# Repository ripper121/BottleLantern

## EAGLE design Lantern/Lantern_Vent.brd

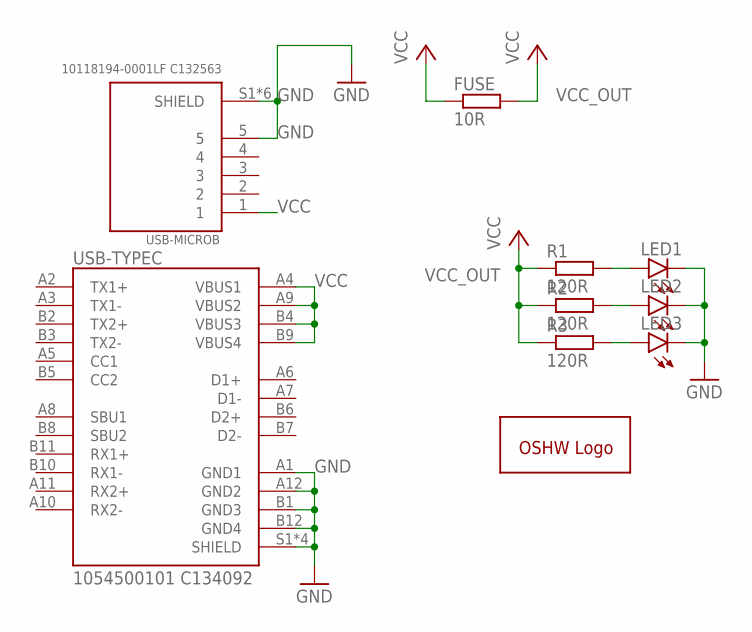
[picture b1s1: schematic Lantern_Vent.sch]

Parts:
FUSE: 10R; R0805
GOLD_ORB_SM1: OSHWLOGOLOGO5MM; OSHW_5MM
LED1, LED2, LED3: LEDCHIP-LED0805; CHIP-LED0805
R1, R2, R3: 120R; R0805
USB-MICROB: 10118194-0001LF C132563; AMPHENOL_10118194-0001LF
USB-TYPEC: 1054500101 C134092; MOLEX_105450-0101

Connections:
GND: LED1.C, LED2.C, LED3.C, USB-MICROB.5, USB-MICROB.S1 (SHIELD), USB-MICROB.S2 (SHIELD), USB-MICROB.S3 (SHIELD), USB-MICROB.S4 (SHIELD), USB-MICROB.S5 (SHIELD), USB-MICROB.S6 (SHIELD), USB-TYPEC.A1 (GND1), USB-TYPEC.A12 (GND2), USB-TYPEC.B1 (GND3), USB-TYPEC.B12 (GND4), USB-TYPEC.S1 (SHIELD), USB-TYPEC.S2 (SHIELD), USB-TYPEC.S3 (SHIELD), USB-TYPEC.S4 (SHIELD)
unnamed: LED1.A, R1.2
unnamed: LED2.A, R2.2
unnamed: LED3.A, R3.2
VCC: FUSE.1, USB-MICROB.1, USB-TYPEC.A4 (VBUS1), USB-TYPEC.A9 (VBUS2), USB-TYPEC.B4 (VBUS3), USB-TYPEC.B9 (VBUS4)
VCC_OUT: FUSE.2, R1.1, R2.1, R3.1

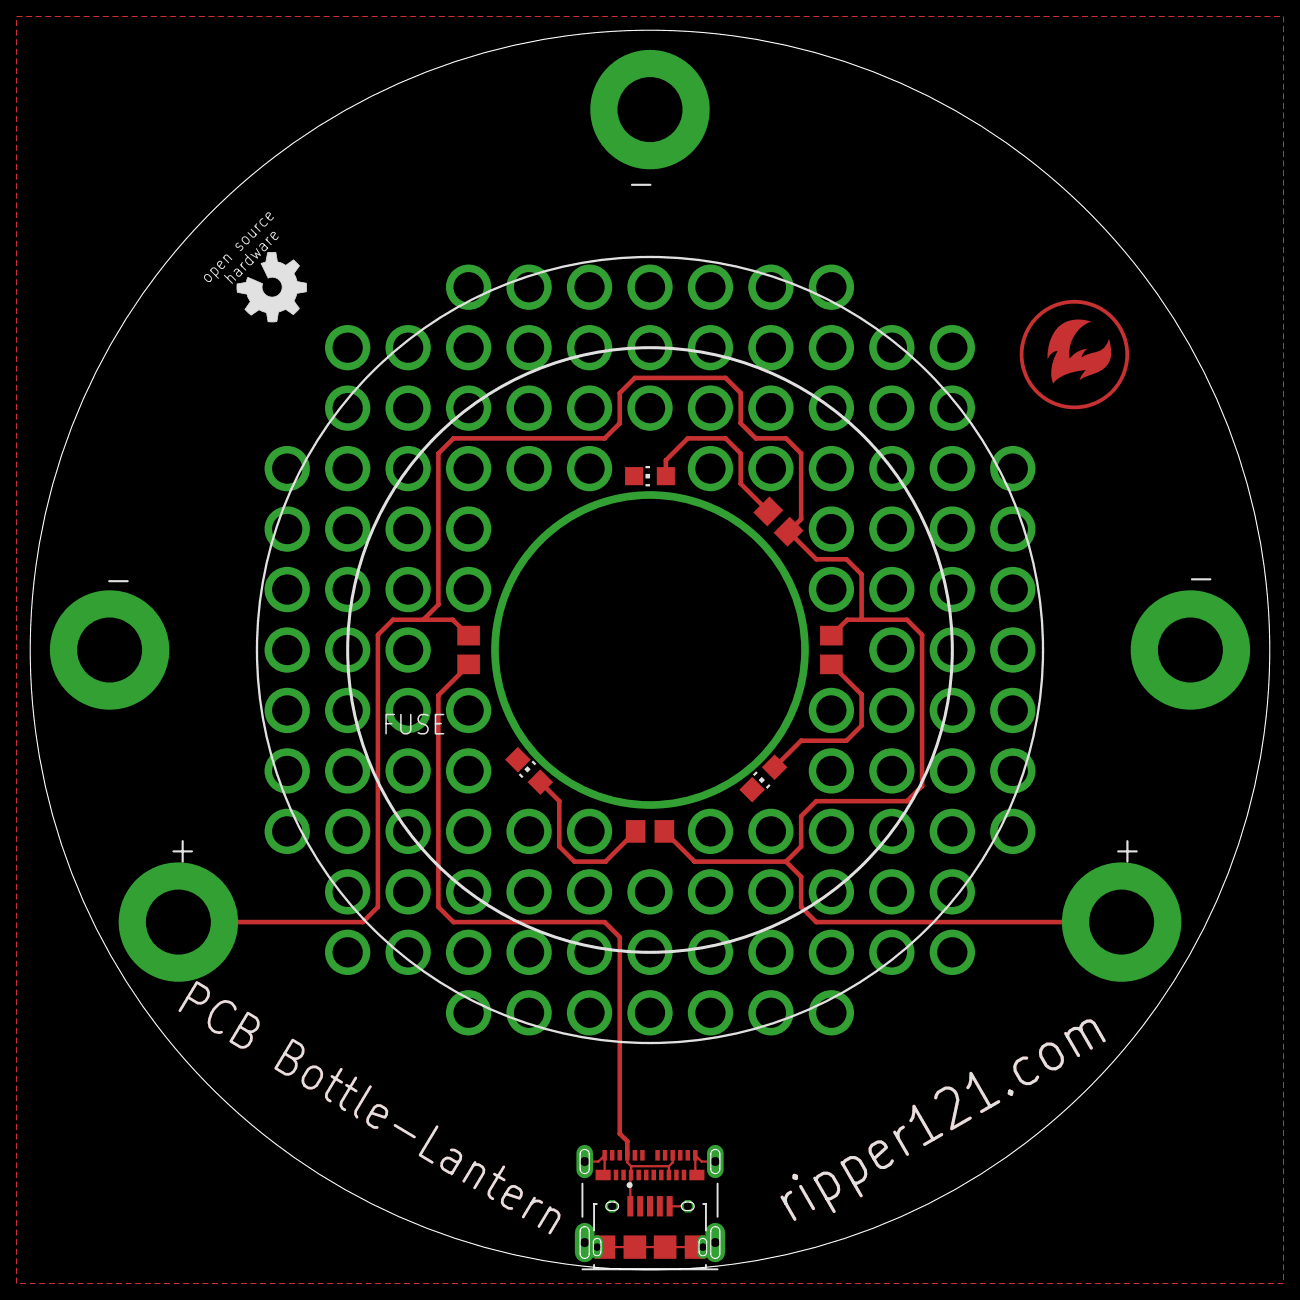
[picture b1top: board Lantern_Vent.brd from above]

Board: 2 copper layers, 82.0 x 82.0 mm, 10 parts (0 on the bottom side), 6 nets.

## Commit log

2021-01-07 first version
2021-01-07 Render
2021-01-15 Fixed Resistors
2021-01-15 DRC fix
2021-01-16 Added Fuse
2021-02-25 update 0127
